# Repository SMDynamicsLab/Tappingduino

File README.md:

# Tappingduino
## A versatile shield for paced finger tapping experiments with Arduino

Paula Caral [1], Tomás Correa Morales [1], Paz García Lodi Fe [1], Ariel D. Silva [2,4], Ulises Bussi [2], Ignacio Spiousas [3,4], and Rodrigo Laje [2,4]

[1] Departamento de Física, FCEN, Universidad de Buenos Aires, Argentina  
[2] Laboratorio de Dinámica Sensomotora, Departamento de Ciencia y Tecnología, Universidad Nacional de Quilmes, Argentina  
[3] Laboratorio del Tiempo y la Experiencia, Universidad de San Andrés, Argentina  
[4] CONICET, Argentina

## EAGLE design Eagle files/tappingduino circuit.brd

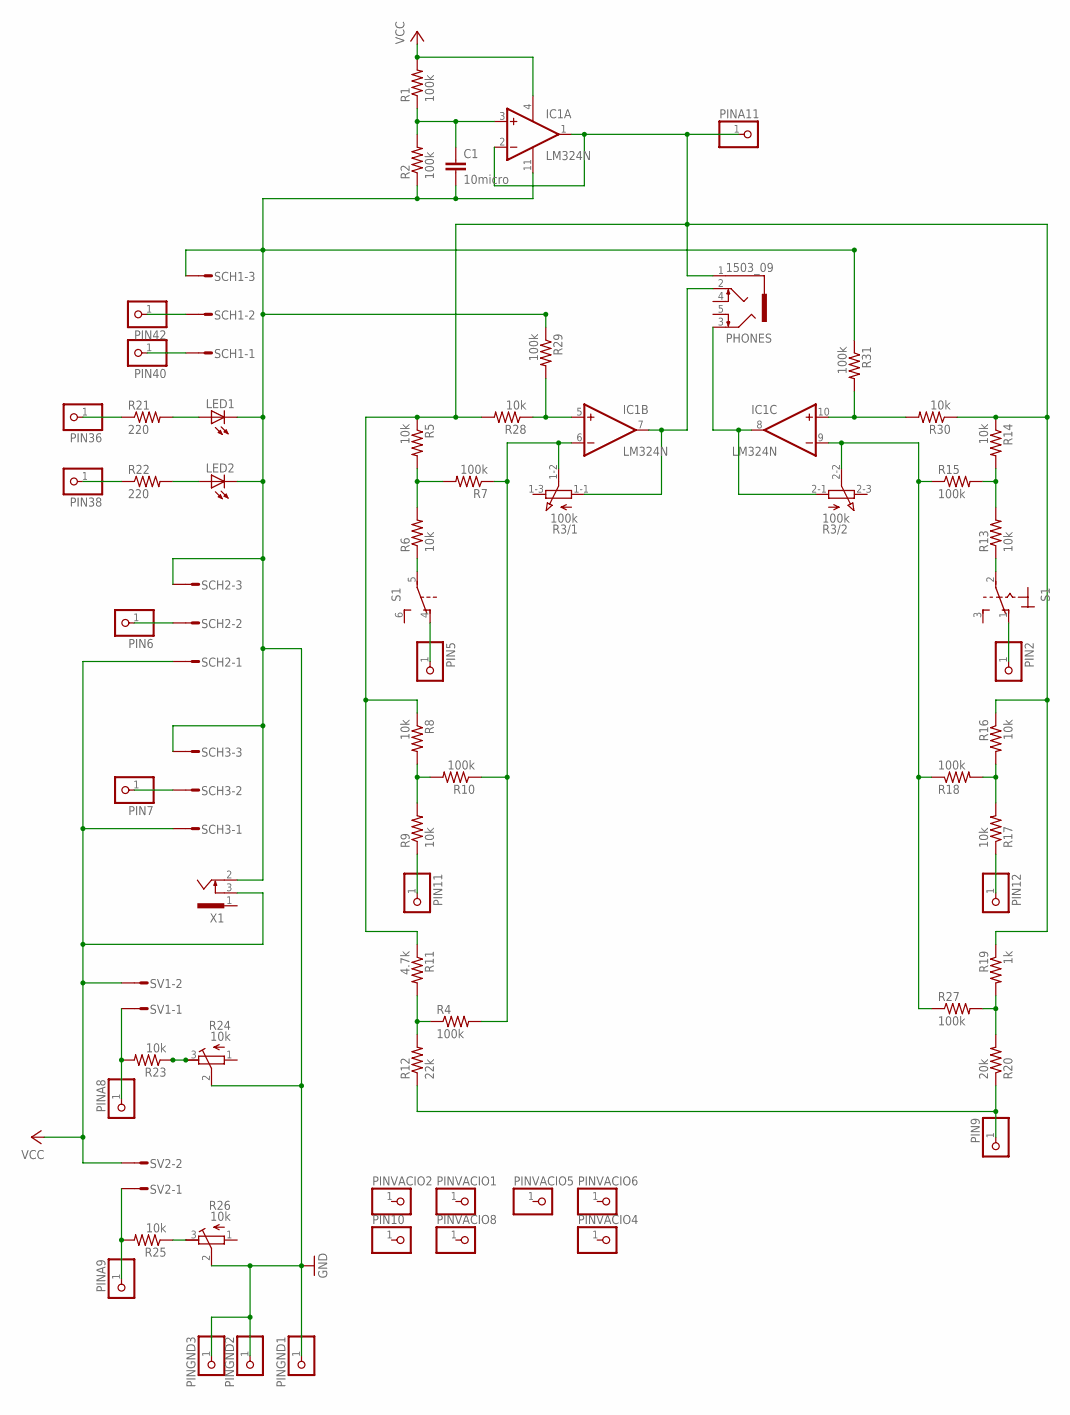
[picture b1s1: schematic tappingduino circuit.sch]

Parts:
C1: 10micro; C025-030X050
IC1: LM324N; DIL14
LED1, LED2: LED_ELD260; LED_LD260
PHONES: 1503_09
PIN2, PIN5, PIN6, PIN7, PIN9, PIN10, PIN11, PIN12, PIN36, PIN38, PIN40, PIN42: PINHD-1X1; 1X01
PINA8, PINA9, PINA11: PINHD-1X1; 1X01
PINGND1, PINGND2, PINGND3: PINHD-1X1; 1X01
PINVACIO1, PINVACIO2, PINVACIO4, PINVACIO5, PINVACIO6, PINVACIO8: PINHD-1X1; 1X01
R1, R2, R4, R7, R10, R15, R18, R27, R29, R31: 100k; 0207/7
R3: 100k; 3RP/1610G
R5, R6, R8, R9, R13, R14, R16, R17, R23, R25, R28, R30: 10k; 0207/7
R11: 4.7k; 0207/7
R12: 22k; 0207/7
R19: 1k; 0207/7
R20: 20k; 0207/7
R21, R22: 220; 0207/7
R24, R26: 10k; RTRIM64W
S1: 320-938
SCH1, SCH2, SCH3: L03P
SV1, SV2: L02P
X1: SCD-014A; SCD-014-A

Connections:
GND: C1.2, IC1.11 (V-), LED1.K (C), LED2.K (C), PINGND1.1, PINGND2.1, PINGND3.1, R2.1, R24.2 (S), R26.2 (S), R29.1, R31.1, SCH1.3, SCH2.3, SCH3.3, X1.2
unnamed: C1.1, IC1.3 (+IN), R1.1, R2.2
unnamed: R25.1, R26.3 (E)
unnamed: PIN11.1, R9.1
unnamed: IC1.6 (-IN), R3.1-2 (S), R4.2, R7.1, R10.1
unnamed: R5.2, R6.2, R7.2
unnamed: R6.1, S1.5
unnamed: PIN5.1, S1.4 (O)
unnamed: IC1.1 (OUT), IC1.2 (-IN), PHONES.1, PINA11.1, R5.1, R8.1, R11.1, R14.1, R16.1, R19.1, R28.2, R30.1
unnamed: R8.2, R9.2, R10.2
unnamed: IC1.10 (+IN), R30.2, R31.2
unnamed: R4.1, R11.2, R12.2
unnamed: IC1.9 (-IN), R3.2-2 (S), R15.1, R18.1, R27.1
unnamed: R13.2, R14.2, R15.2
unnamed: R13.1, S1.2
unnamed: PIN2.1, S1.1 (O)
unnamed: IC1.5 (+IN), R28.1, R29.2
unnamed: R19.2, R20.2, R27.2
unnamed: R16.2, R17.2, R18.2
unnamed: PIN12.1, R17.1
unnamed: PIN9.1, R12.1, R20.1
unnamed: PIN42.1, SCH1.2
unnamed: PIN40.1, SCH1.1
unnamed: LED1.A, R21.2
unnamed: PIN36.1, R21.1
unnamed: LED2.A, R22.2
unnamed: PIN38.1, R22.1
unnamed: PIN7.1, SCH3.2
unnamed: PIN6.1, SCH2.2
unnamed: IC1.8 (OUT), PHONES.3, R3.2-1 (A)
unnamed: PINA8.1, R23.2, SV1.1
unnamed: R23.1, R24.3 (E)
unnamed: PINA9.1, R25.2, SV2.1
unnamed: IC1.7 (OUT), PHONES.2, R3.1-1 (A)
VCC: IC1.4 (V+), R1.2, SCH2.1, SCH3.1, SV1.2, SV2.2, X1.3

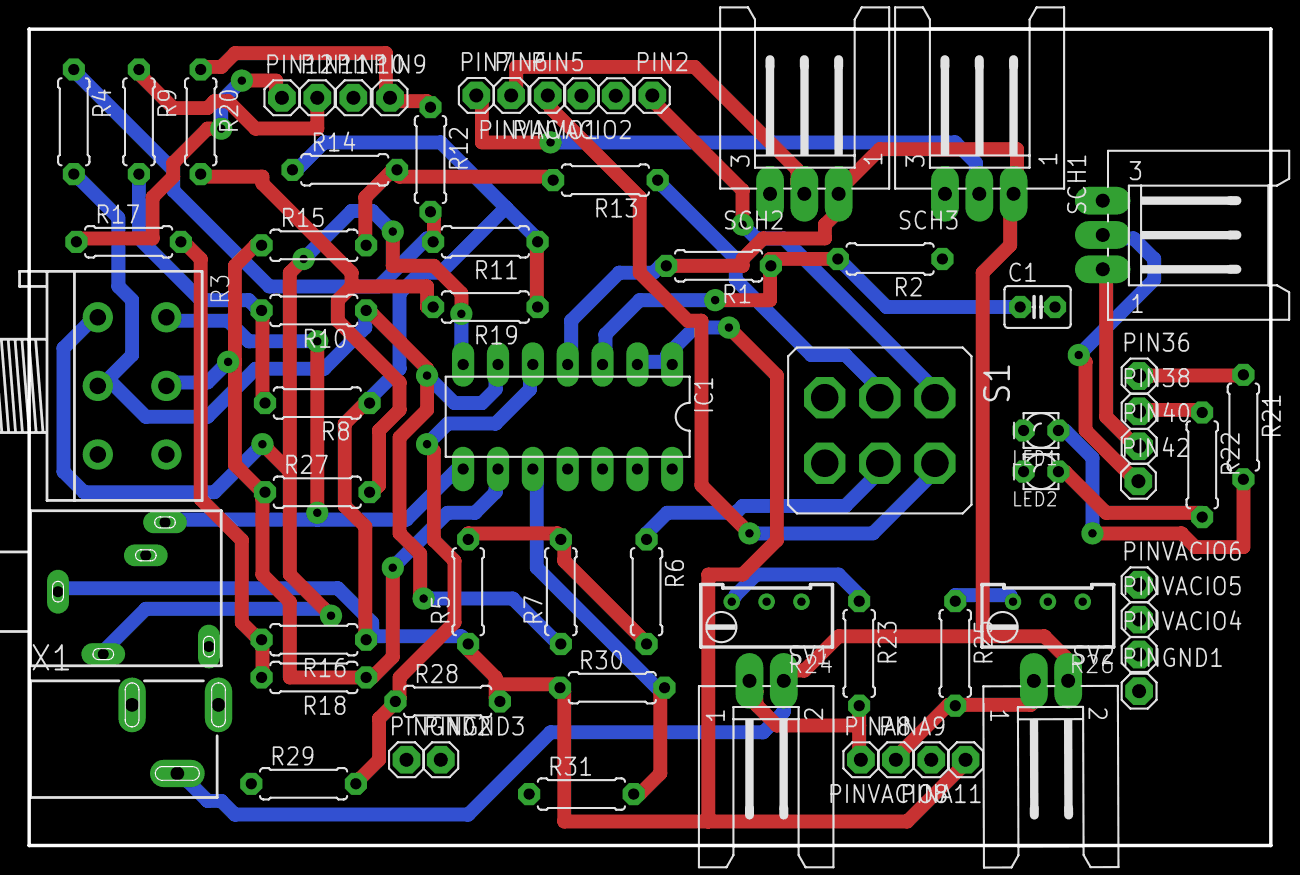
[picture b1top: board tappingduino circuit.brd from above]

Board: 2 copper layers, 90.5 x 59.5 mm, 67 parts (0 on the bottom side), 35 nets.

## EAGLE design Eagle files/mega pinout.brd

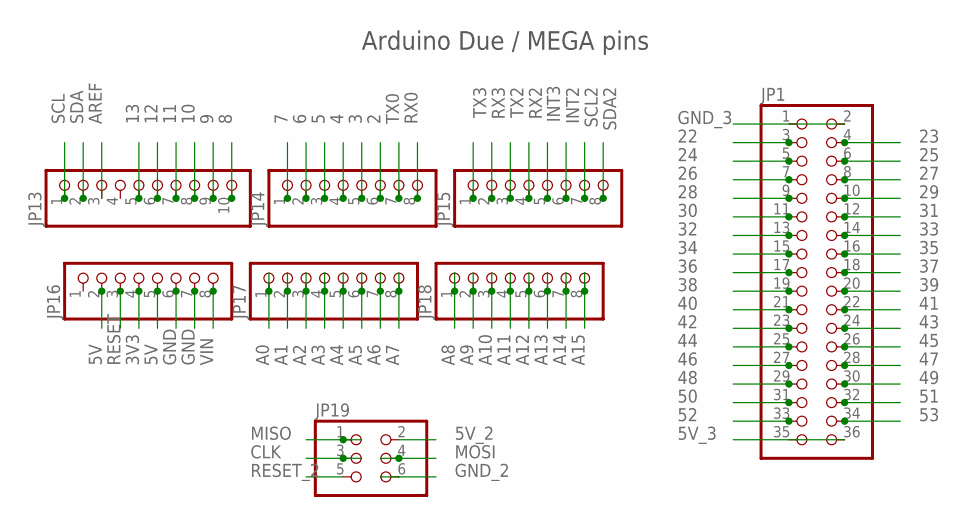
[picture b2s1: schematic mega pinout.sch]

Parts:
JP1: PINHD-2X18; 2X18
JP13: PINHD-1X10; 1X10
JP14, JP15, JP16, JP17, JP18: PINHD-1X8; 1X08
JP19: PINHD-2X3; 2X03

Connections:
2: JP14.6
3: JP14.5
3V3: JP16.4
4: JP14.4
5: JP14.3
5V: JP16.2, JP16.5
5V_2: JP19.2
5V_3: JP1.36
6: JP14.2
7: JP14.1
8: JP13.10
9: JP13.9
10: JP13.8
11: JP13.7
12: JP13.6
13: JP13.5
22: JP1.3
23: JP1.4
24: JP1.5
25: JP1.6
26: JP1.7
27: JP1.8
28: JP1.9
29: JP1.10
30: JP1.11
31: JP1.12
32: JP1.13
33: JP1.14
34: JP1.15
35: JP1.16
36: JP1.17
37: JP1.18
38: JP1.19
39: JP1.20
40: JP1.21
41: JP1.22
42: JP1.23
43: JP1.24
44: JP1.25
45: JP1.26
46: JP1.27
47: JP1.28
48: JP1.29
49: JP1.30
50: JP1.31
51: JP1.32
52: JP1.33
53: JP1.34
A0: JP17.1
A1: JP17.2
A2: JP17.3
A3: JP17.4
A4: JP17.5
A5: JP17.6
A6: JP17.7
A7: JP17.8
A8: JP18.1
A9: JP18.2
A10: JP18.3
A11: JP18.4
A12: JP18.5
A13: JP18.6
A14: JP18.7
A15: JP18.8
AREF: JP13.3
CLK: JP19.3
GND: JP16.6, JP16.7
GND_3: JP1.2
INT2: JP15.6
INT3: JP15.5
MISO: JP19.1
MOSI: JP19.4
RESET: JP16.3
RESET_2: JP19.5
RX0: JP14.8
RX2: JP15.4
RX3: JP15.2
SCL: JP13.1
SCL2: JP15.7
SDA: JP13.2
SDA2: JP15.8
TX0: JP14.7
TX2: JP15.3
TX3: JP15.1
VIN: JP16.8

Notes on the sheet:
Arduino Due / MEGA pins

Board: 2 copper layers, 8 parts (0 on the bottom side), 2 nets, no tracks yet.

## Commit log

2023-10-24 added code, manuscript, Eagle files
2023-10-24 updated manuscript and README
2023-10-31 updated manuscript
2024-07-06 remove old license
2024-07-06 add new license
